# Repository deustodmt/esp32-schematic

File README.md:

# Proyecto PCB para Moto Eléctrica de Competición

Este repositorio documenta el diseño y desarrollo de una PCB para una moto eléctrica de competición. El objetivo principal es crear una placa personalizada basada en la ESP32-S3-DevKitC-1 que integre varios sensores y módulos esenciales para la recolección de datos, comunicación y navegación del vehículo.

---

## 📈 Estado actual del proyecto

---

## 🪤 Módulos incluidos en el diseño

### ESP32-S3-DevKitC-1
Microcontrolador principal encargado de recopilar datos de los sensores, procesarlos y transmitir información vía CAN o WiFi/Bluetooth. Este microcontrolador se elige por su versatilidad, potencia y conectividad.

### CAN (Controller Area Network)
Permite la comunicación robusta y rápida entre la ESP32 y otros controladores del sistema, como el BMS (Battery Management System) o la ECU (Electronic Control Unit). Se utiliza el transceptor TJA1051T para traducir las señales lógicas de la ESP32 al bus CAN.

### IMU (Unidad de Medición Inercial)
Usando el módulo MPU-6000, permite conocer la aceleración y rotación de la moto en tiempo real. Es fundamental para la telemetría y el análisis de dinámica del vehículo.

### GPS
El módulo GN-2630G proporciona la localización de la moto mediante señal satelital. Este dato es crucial para conocer la trayectoria y velocidad en pista.

### ENV (Sensor ambiental) *(Añadir cuando se incluya)*
Este módulo recogerá datos como temperatura, presión y humedad, los cuales podrían ser útiles para ajustar el rendimiento de la moto o estudiar las condiciones en pista.

---

## 📝 Diseño de la PCB

El diseño de la PCB ha sido elaborado buscando:
- **Minimizar interferencias** entre módulos sensibles como el GPS o la IMU.
- **Facilitar el ruteado** de las pistas, manteniendo las pistas de alimentación más anchas y las de señal bien definidas.
- **Disposición funcional** de los componentes, agrupando por función: comunicación, sensores, alimentación.
- **Posibilidad de depuración** y pruebas: se dejan pines de testeo accesibles.

Los principios seguidos incluyen buenas prácticas de colocación de condensadores de desacoplo, rutas cortas para señales críticas, y separación adecuada entre señales analógicas y digitales.

---

## ⚖️ Uso de KiCad

Para el diseño del proyecto se ha utilizado **KiCad**, una suite libre de diseño de PCB.

### Metodología de trabajo:
1. **Esquemático:** Creación del diagrama esquemático conectando todos los componentes.
2. **Asignación de huellas (footprints):** Asociación de cada componente con su huella física.
3. **Diseño de la PCB:** Colocación y ruteado de las pistas.
4. **Verificación DRC/ERC:** Comprobaciones de reglas eléctricas y de diseño.
5. **Exportación de archivos Gerber:** Preparación para fabricación.
6. **Renderizado 3D:** Visualización realista de la placa antes de su fabricación.

### Plugins útile:
- **KiCad-Diff:** Para ver cambios entre commits.
- **Interactive HTML BOM:** Genera una lista de materiales navegable visualmente.
- **SnapEDA / SamacSys Plugin:** Importación directa de modelos de componentes.
- **easyeda2kicad:** Copia los componentes de LCSC para importar las huellas y modelos https://github.com/uPesy/easyeda2kicad.py

### Comando recomendable para linux:
Para la implementación de easyeda2kicad
<pre>
kicadcomponent() {
    for arg in "$@"; do
        if [[ $arg == "-h" ]]; then
            echo "Use: kicadcomponent <lcsc_id> <output_location>"
            echo "Example: kicadcomponent C12345 ~/Documents/easyeda2kicad"
            echo "The output location must be the location of the lib and the name of the files"
            echo "Supose the lib name is easyeda2kicad, then the output will be:"
            echo "easyeda2kicad.pretty in ~/Documents"
            echo "easyeda2kicad.kicad_sym in ~/Documents"
            echo "easyeda2kicad.3dshape in ~/Documents"
            echo "If the lib name is . then all files will be hidden"
            return 0
        fi
    done
    
    # MODIFY THE LOCATION OF THE VENV
    source ~/Projects/venv/easyeda-env/bin/activate
    easyeda2kicad --full --overwrite --lcsc_id="$1" --output="$2"
}
</pre>

---

## 🚚 Fabricación de PCBs

Para la fabricación se recomienda:

- **JLCPCB**: https://jlcpcb.com/
  - Plataforma popular y asequible para fabricar placas PCB a partir de archivos Gerber.
- **LCSC**: https://lcsc.com/
  - Proveedor de componentes electrónicos que permite integración directa con JLCPCB para el montaje.
- **SnapMagic / SamacSys**: https://www.snapeda.com/
  - Herramienta para obtener símbolos, huellas y modelos 3D de componentes para integrarlos en KiCad.

---

## 📊 Conceptos básicos del diseño de PCBs

### Esquema de componentes (Schematic)
Representación lógica de cómo se conectan los componentes del circuito. No representa distancias ni posiciones físicas.

### Diseño de la PCB
Proceso de colocación física de los componentes y trazado de pistas que conectan los nodos definidos en el esquema.

### Renderizado 3D
Visualización tridimensional de la placa para comprobar posibles errores mecánicos y facilitar presentaciones.

### Archivos Gerber
Conjunto de archivos estándar que describen la geometría y capas de una placa PCB. Son enviados al fabricante para producir la placa.

---

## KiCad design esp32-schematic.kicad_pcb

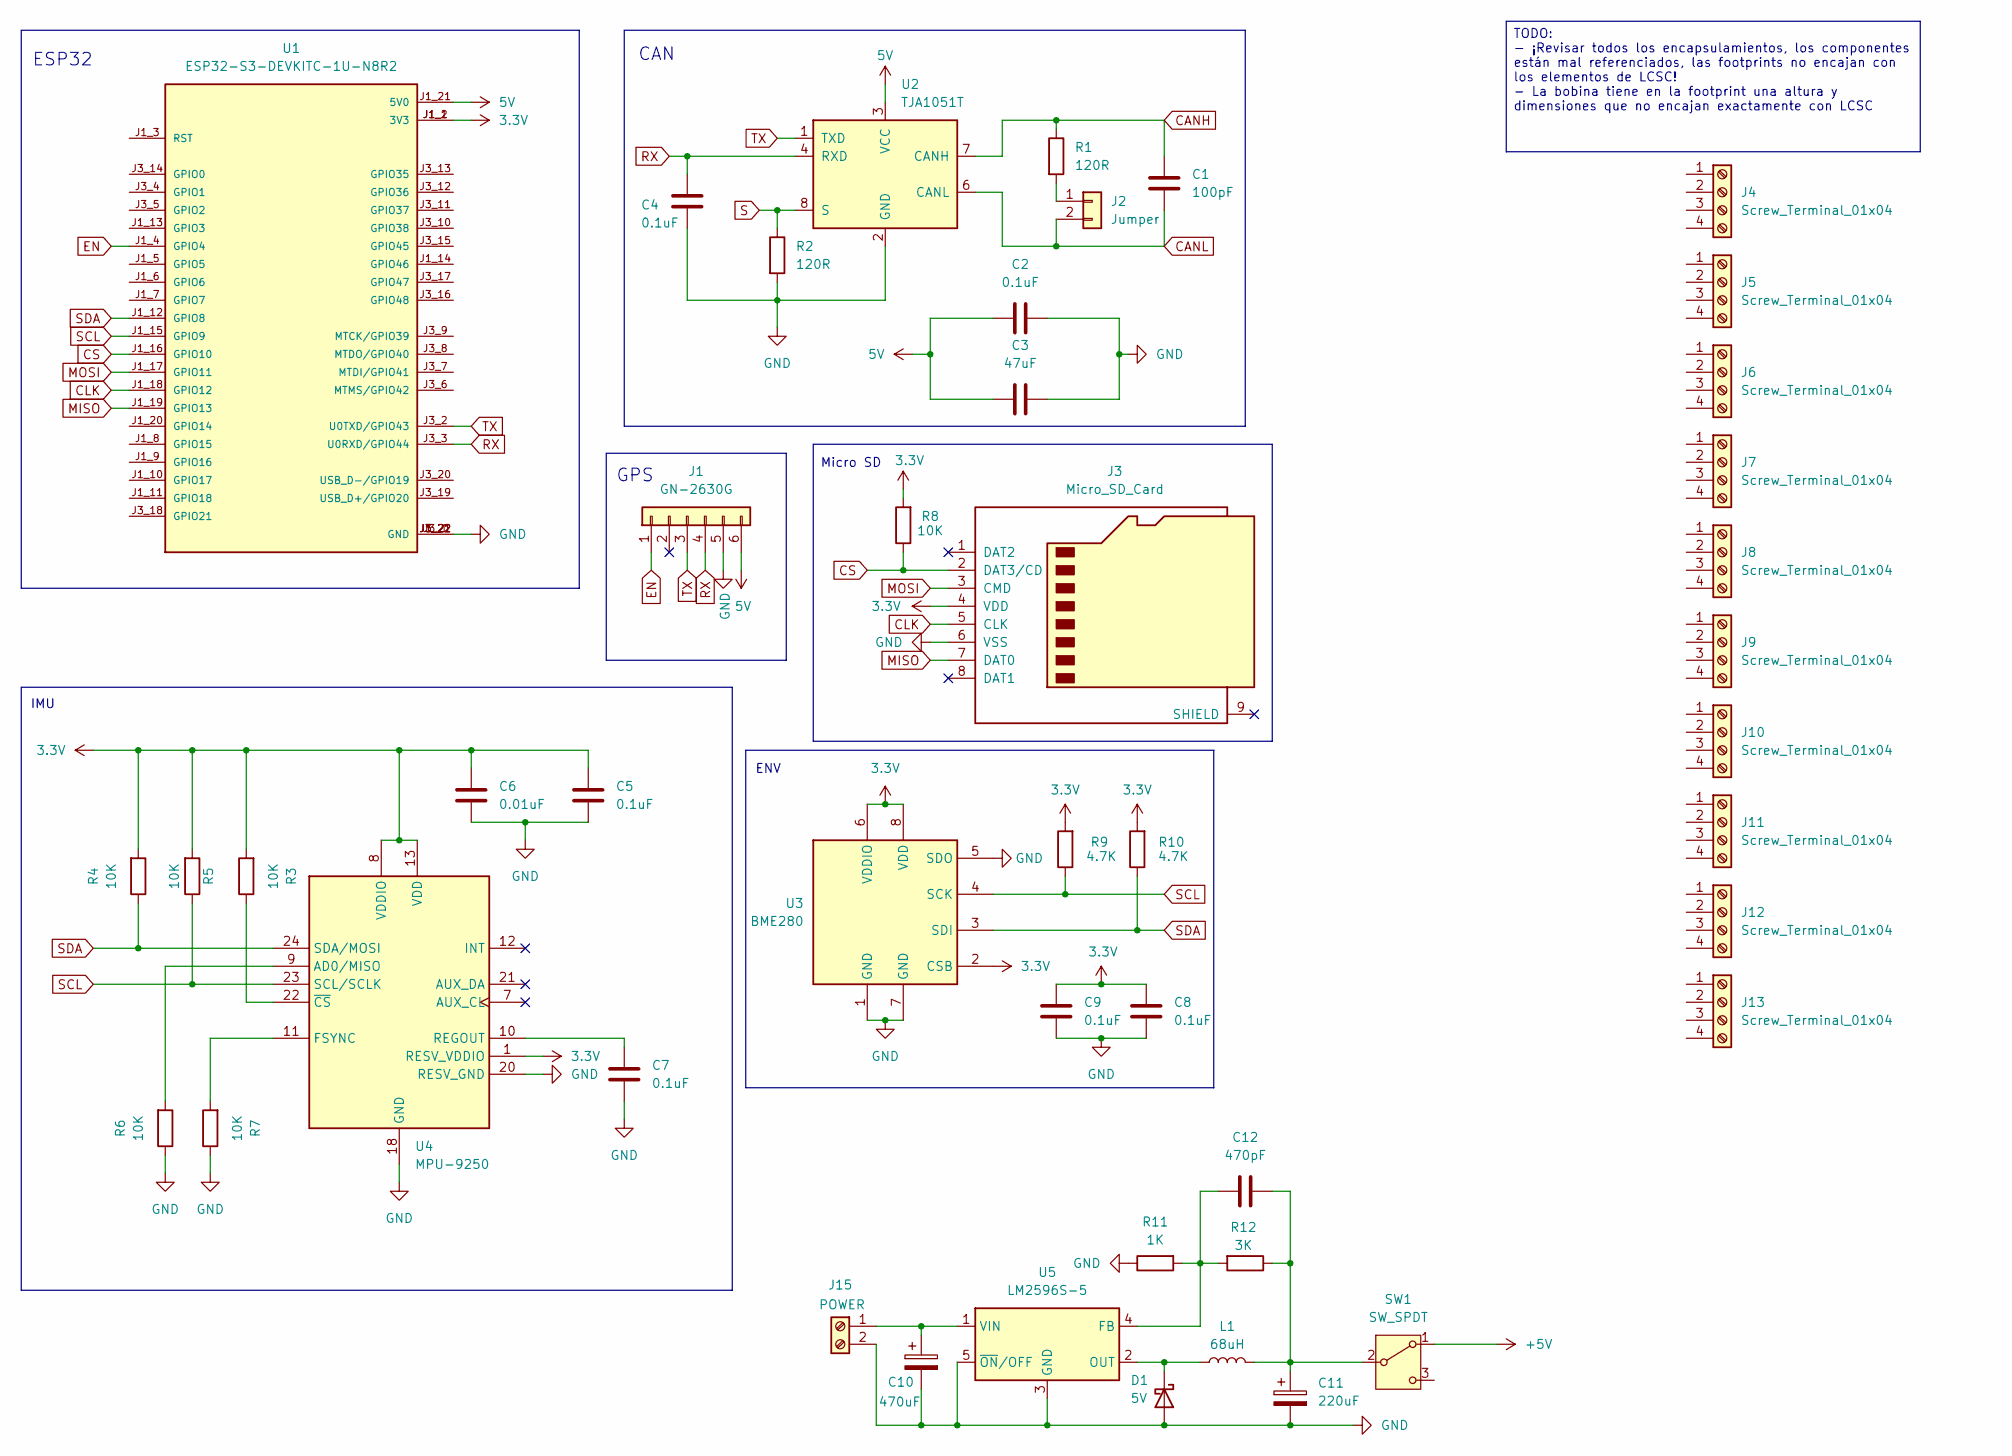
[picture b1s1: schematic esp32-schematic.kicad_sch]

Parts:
C1: 100pF; C_0805_2012Metric
C2, C4, C5, C7, C8, C9: 0.1uF; C_0805_2012Metric
C3: 47uF; C_0805_2012Metric
C6: 0.01uF; C_0805_2012Metric
C10: 470uF; CP_Radial_D10.0mm_P5.00mm
C11: 220uF; CP_Elec_10x10
C12: 470pF; C_0201_0603Metric
D1: 5V; D_SMA
J1: GN-2630G; PinHeader_1x06_P2.54mm_Vertical
J2: Jumper; PinHeader_1x02_P1.00mm_Vertical
J3: Micro_SD_Card; microSD_HC_Molex_104031-0811
J4, J5, J6, J7, J8, J9, J10, J11, J12, J13: Screw_Terminal_01x04; TerminalBlock_Phoenix_MKDS-1,5-4-5.08_1x04_P5.08mm_Horizont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
J15: POWER; TerminalBlock_Phoenix_PT-1,5-2-3.5-H_1x02_P3.50mm_Horizontal
L1: 68uH; L_12x12mm_H6mm
R1, R2: 120R; R_1206_3216Metric
R3, R4, R5, R6, R7, R8: 10K; R_1206_3216Metric
R9, R10: 4.7K; R_1206_3216Metric
R11: 1K; R_0201_0603Metric
R12: 3K; R_Axial_DIN0411_L9.9mm_D3.6mm_P15.24mm_Horizontal
SW1: SW_SPDT; SW_DPDT_CK_JS202011JCQN
U1: ESP32-S3-DEVKITC-1U-N8R2; XCVR_ESP32-S3-DEVKITC-1U-N8R2; PARTREV 5.3
U2: TJA1051T; SOIC-8_3.9x4.9mm_P1.27mm
U3: BME280; Bosch_LGA-8_2.5x2.5mm_P0.65mm_ClockwisePinNumbering
U4: MPU-9250; InvenSense_QFN-24_3x3mm_P0.4mm
U5: LM2596S-5; TO-263-5_TabPin3

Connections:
3.3V: C5.1, C6.1, C8.1, C9.1, J3.4 (VDD), R3.2, R4.2, R5.2, R8.2, R9.2, R10.2, U1.J1_1 (3V3), U1.J1_2 (3V3), U3.2 (CSB), U3.6 (VDDIO), U3.8 (VDD), U4.1 (RESV_VDDIO), U4.8 (VDDIO), U4.13 (VDD)
5V: C2.1, C3.1, J1.6, U1.J1_21 (5V0), U2.3 (VCC)
+5V: SW1.1 (A)
CANH: C1.1, R1.1, U2.7 (CANH)
CANL: C1.2, J2.2, U2.6 (CANL)
CLK: J3.5 (CLK), U1.J1_18 (GPIO12)
CS: J3.2 (DAT3/CD), R8.1, U1.J1_16 (GPIO10)
EN: J1.1, U1.J1_4 (GPIO4)
GND: C2.2, C3.2, C4.2, C5.2, C6.2, C7.2, C8.2, C9.2, C10.2, C11.2, D1.2 (A), J1.5, J3.6 (VSS), J15.2, R2.2, R6.1, R7.1, R11.1, U1.J1_22 (GND), U1.J3_1 (GND), U1.J3_21 (GND), U1.J3_22 (GND), U2.2 (GND), U3.1 (GND), U3.5 (SDO), U3.7 (GND), U4.18 (GND), U4.20 (RESV_GND), U5.3 (GND), U5.5 (~ON/OFF)
MISO: J3.7 (DAT0), U1.J1_19 (GPIO13)
MOSI: J3.3 (CMD), U1.J1_17 (GPIO11)
unnamed: D1.1 (K), L1.1, U5.2 (OUT)
unnamed: J2.1, R1.2
unnamed: C10.1, J15.1, U5.1 (VIN)
unnamed: C11.1, C12.2, L1.2, R12.1, SW1.2 (B)
unnamed: R6.2, U4.9 (AD0/MISO)
unnamed: R7.2, U4.11 (FSYNC)
unnamed: C7.1, U4.10 (REGOUT)
unnamed: R3.1, U4.22 (~CS)
unnamed: C12.1, R11.2, R12.2, U5.4 (FB)
RX: C4.1, J1.4, U1.J3_3 (U0RXD/GPIO44), U2.4 (RXD)
S: R2.1, U2.8 (S)
SCL: R5.1, R9.1, U1.J1_15 (GPIO9), U3.4 (SCK), U4.23 (SCL/SCLK)
SDA: R4.1, R10.1, U1.J1_12 (GPIO8), U3.3 (SDI), U4.24 (SDA/MOSI)
TX: J1.3, U1.J3_2 (U0TXD/GPIO43), U2.1 (TXD)

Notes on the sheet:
GPS
ESP32
CAN
Micro SD
IMU
ENV
TODO: - ¡Revisar todos los encapsulamientos, los componentes están mal referenciados, las footprints no encajan con los elementos de LCSC! - La bobina tiene en la footprint una altura y dimensiones que no encajan exactamente con LCSC

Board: 2 copper layers, 46 parts (0 on the bottom side), 24 nets, no tracks yet.

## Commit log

2025-04-13 GPS added and CAN in progress
2025-04-13 CAN in progress
2025-04-14 CAN schematic and IMU schematic ready
2025-04-15 Readme Updated
2025-04-26 Micro SD added, IMU is now the MPU-9250, connections were moved in the ESP32 pins and the right footprints were added
2025-04-29 SD slot added, ENV added, issues fixed
2025-04-29 missing footprints added
2025-05-11 DC-DC added, and bornes for the esp32 in progress
2025-05-16 Reorganisation of the project, the v1 will be the test prototype and the v2 will be implementing the devices on the board directly. Also the libraries have been reorganised, each version will share a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
2025-05-17 external power supply entry added, and todo list updated
2025-08-06 quick save
2025-08-06 index file added to identify the footprints of the components easily with a legible name
